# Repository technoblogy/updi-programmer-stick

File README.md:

# UPDI Programmer Stick
A USB-stick sized UPDI programmer, for programming Microchip's new 0-series and 1-series ATtiny chips from the Arduino IDE.
For more information see: http://www.technoblogy.com/show?2OJT

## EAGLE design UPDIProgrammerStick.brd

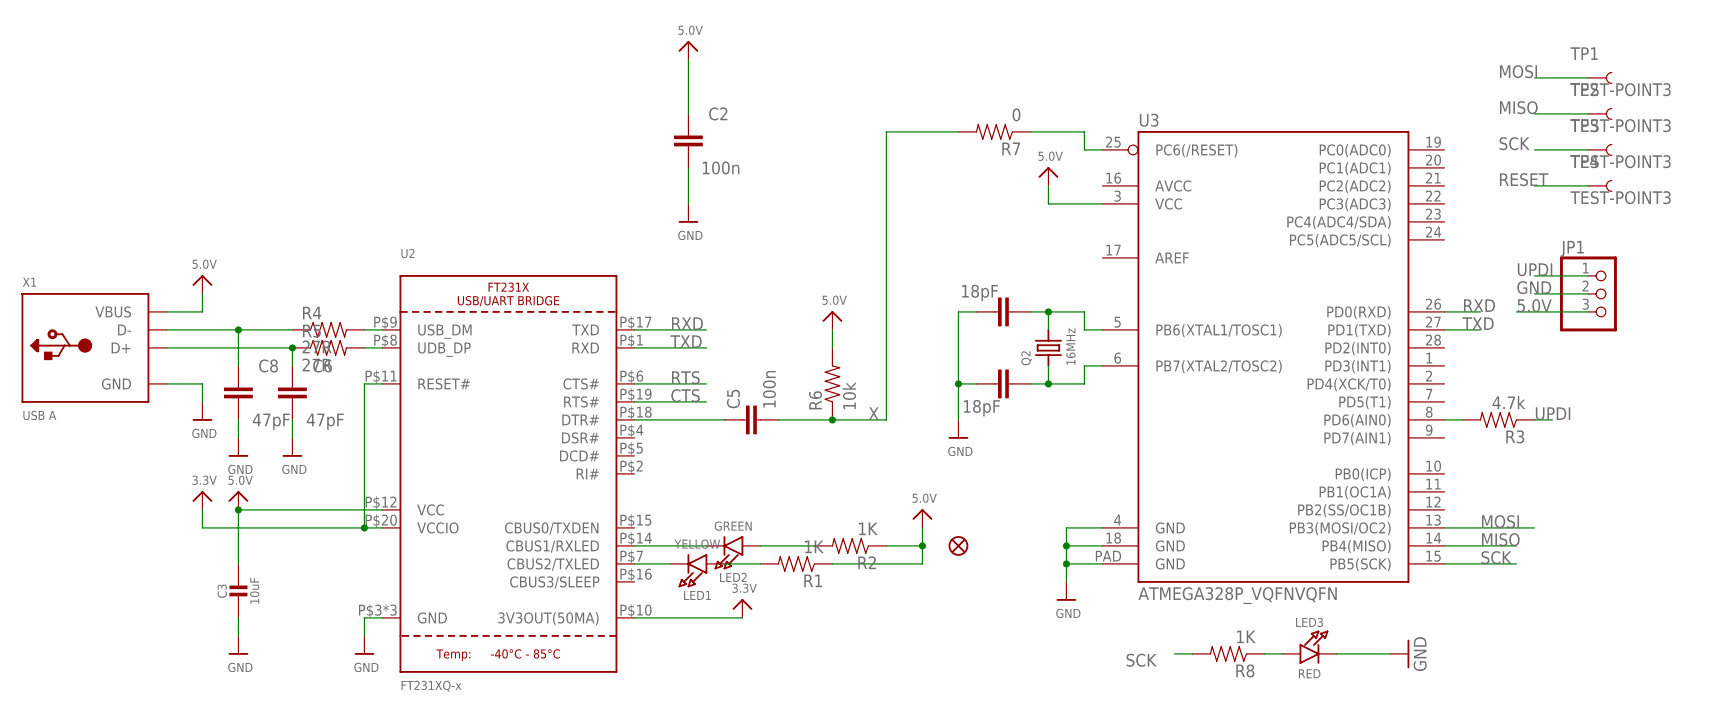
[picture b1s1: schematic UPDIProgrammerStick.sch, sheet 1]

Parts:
C2, C5: 100n; 0603-CAP
C3: 10uF; _0805MP
C6, C8: 47pF; 0603-CAP
C12, C13: 18pF; 0603-CAP
FID2: FIDUCIAL""; FIDUCIAL_1MM
JP1: PINHD-1X3; 1X03
LED1: YELLOW; CHIPLED_0805_NOOUTLINE
LED2: GREEN; CHIPLED_0805_NOOUTLINE
LED3: RED; CHIPLED_0805_NOOUTLINE
Q2: 16MHz; CRYSTAL_3.2X2.5
R1, R2, R8: 1K; 0805
R3: 4.7k; 0805
R4, R5: 27R; 0805
R6: 10k; 0805
R7: 0; 0805
TP1, TP2, TP3, TP4: TEST-POINT3; PAD.03X.03
U2: FT231XQ-x; QFN20_4MM
U3: ATMEGA328P_VQFNVQFN; VQFN-28
X1: USB A; USB_A-THM

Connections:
3.3V: U2.P$10 (3V3OUT(50MA)), U2.P$11 (RESET#), U2.P$20 (VCCIO)
5.0V: C2.1, C3.1, JP1.3, R1.1, R2.1, R6.2, U2.P$12 (VCC), U3.3 (VCC), X1.VBUS
CTS: U2.P$19 (RTS#)
GND: C2.2, C3.2, C6.2, C8.2, C12.2, C13.2, JP1.2, LED3.C, U2.P$3 (GND), U2.P$13 (GND), U2.P$21 (GND), U3.4 (GND), U3.18 (GND), U3.PAD (GND), X1.GND
MISO: TP2.P$1, U3.14 (PB4(MISO))
MOSI: TP1.P$1, U3.13 (PB3(MOSI/OC2))
unnamed: LED2.A, R2.2
unnamed: R3.2, U3.8 (PD6(AIN0))
unnamed: LED1.A, R1.2
unnamed: LED1.C, U2.P$7 (CBUS2/TXLED)
unnamed: LED2.C, U2.P$14 (CBUS1/RXLED)
unnamed: C8.1, R4.1, X1.D-
unnamed: C6.1, R5.1, X1.D+
unnamed: C12.1, Q2.2, U3.5 (PB6(XTAL1/TOSC1))
unnamed: C13.1, Q2.1, U3.6 (PB7(XTAL2/TOSC2))
unnamed: R5.2, U2.P$8 (UDB_DP)
unnamed: LED3.A, R8.1
unnamed: R4.2, U2.P$9 (USB_DM)
unnamed: C5.1, U2.P$18 (DTR#)
RESET: R7.1, TP4.P$1, U3.25 (PC6(/RESET))
RTS: U2.P$6 (CTS#)
RXD: U2.P$17 (TXD), U3.26 (PD0(RXD))
SCK: R8.2, TP3.P$1, U3.15 (PB5(SCK))
TXD: U2.P$1 (RXD), U3.27 (PD1(TXD))
UPDI: JP1.1, R3.1
X: C5.2, R6.1, R7.2

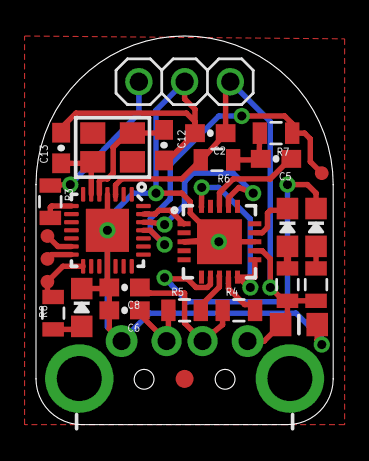
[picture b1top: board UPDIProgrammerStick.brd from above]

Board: 2 copper layers, 16.5 x 21.6 mm, 28 parts (0 on the bottom side), 24 nets.

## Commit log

2019-10-30 Version 1 - 30th October 2019

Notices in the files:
parts and their libraries:
microbuilder: This work is placed in the public domain, and may be freely used for commercial and non-commercial work with the following conditions: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
SparkFun-Capacitors: Licensing: CC v3.0 Share-Alike You are welcome to use this library for commercial purposes.
